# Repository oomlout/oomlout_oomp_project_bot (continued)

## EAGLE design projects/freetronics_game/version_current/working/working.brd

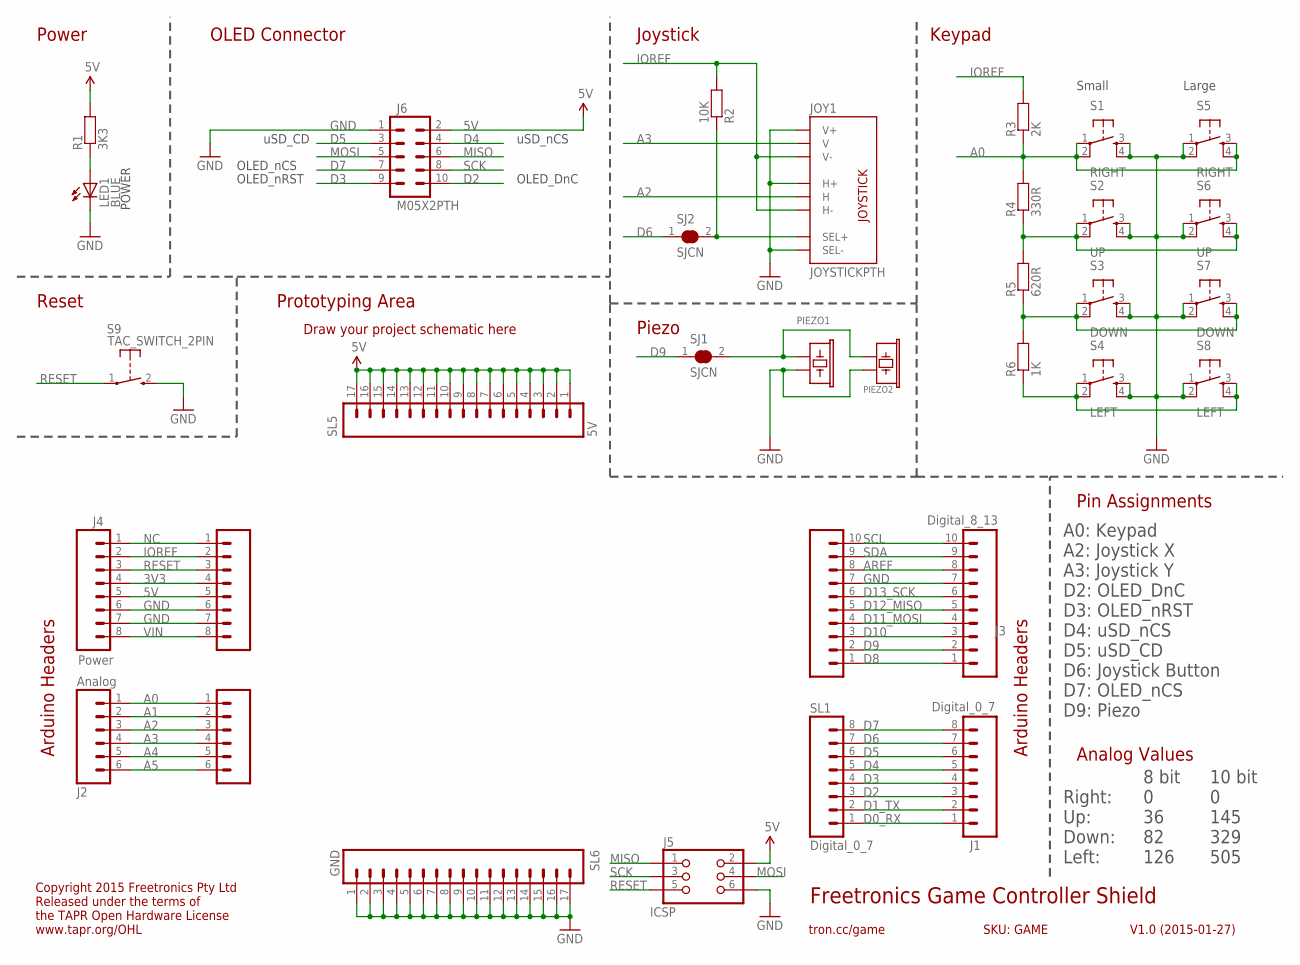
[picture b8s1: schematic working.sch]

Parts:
J1: Digital_0_7; 1X08
J2: Analog; 1X06
J3: Digital_8_13; 1X10
J4: Power; 1X08
J5: ICSP; 2X03PTH
J6: M05X2PTH; AVR_ICSP
JOY1: JOYSTICKPTH; JOYSTICK
LED1: BLUE; LED-0603
PIEZO1: BUZZERSMD12X12; BUZZER-12X12-SMT
PIEZO2: PIEZO12MM
R1: 3K3; 0603
R2: 10K; 0603
R3: 2K; 0603
R4: 330R; 0603
R5: 620R; 0603
R6: 1K; 0603
S1: RIGHT; TACTILE-PTH
S2: UP; TACTILE-PTH
S3: DOWN; TACTILE-PTH
S4: LEFT; TACTILE-PTH
S5: RIGHT; TACTILE-PTH-12MM
S6: UP; TACTILE-PTH-12MM
S7: DOWN; TACTILE-PTH-12MM
S8: LEFT; TACTILE-PTH-12MM
S9: TAC_SWITCH_2PIN; TACTILE_SWITCH_SMD_2PIN_TINY
SJ1, SJ2: SJCN; SJC
SL1: Digital_0_7; 1X08
SL2: Analog; 1X06
SL3: Digital_8_13; 1X10
SL4: Power; 1X08
SL5: 5V; 1X17
SL6: GND; 1X17

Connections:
3V3: J4.4, SL4.4
5V: J4.5, J5.2, J6.2, R1.2, SL4.5, SL5.1, SL5.2, SL5.3, SL5.4, SL5.5, SL5.6, SL5.7, SL5.8, SL5.9, SL5.10, SL5.11, SL5.12, SL5.13, SL5.14, SL5.15, SL5.16, SL5.17
A0: J2.1, R3.1, R4.2, S1.1, S1.2, S5.3, S5.4, SL2.1
A1: J2.2, SL2.2
A2: J2.3, JOY1.H2 (H), SL2.3
A3: J2.4, JOY1.V2 (V), SL2.4
A4: J2.5, SL2.5
A5: J2.6, SL2.6
AREF: J3.8, SL3.8
D0_RX: J1.1, SL1.1
D1_TX: J1.2, SL1.2
D2: J1.3, J6.10, SL1.3
D3: J1.4, J6.9, SL1.4
D4: J1.5, J6.4, SL1.5
D5: J1.6, J6.3, SL1.6
D6: J1.7, SJ2.1, SL1.7
D7: J1.8, J6.7, SL1.8
D8: J3.1, SL3.1
D9: J3.2, SJ1.1, SL3.2
D10: J3.3, SL3.3
D11_MOSI: J3.4, SL3.4
D12_MISO: J3.5, SL3.5
D13_SCK: J3.6, SL3.6
GND: J3.7, J4.6, J4.7, J5.6, J6.1, JOY1.B2A (SEL-), JOY1.H1 (H+), JOY1.V1 (V+), LED1.C, PIEZO1.1, PIEZO2.2, S1.3, S1.4, S2.3, S2.4, S3.3, S3.4, S4.3, S4.4, S5.1, S5.2, S6.1, S6.2, S7.1, S7.2, S8.1, S8.2, S9.2 (S), SL3.7, SL4.6, SL4.7, SL6.1, SL6.2, SL6.3, SL6.4, SL6.5, SL6.6, SL6.7, SL6.8, SL6.9, SL6.10, SL6.11, SL6.12, SL6.13, SL6.14, SL6.15, SL6.16, SL6.17
IOREF: J4.2, JOY1.H3 (H-), JOY1.V3 (V-), R2.2, R3.2, SL4.2
MISO: J5.1, J6.6
MOSI: J5.4, J6.5
unnamed: LED1.A, R1.1
unnamed: PIEZO1.2, PIEZO2.1, SJ1.2
unnamed: JOY1.B1A (SEL+), R2.1, SJ2.2
unnamed: R6.1, S4.1, S4.2, S8.3, S8.4
unnamed: R5.1, R6.2, S3.1, S3.2, S7.3, S7.4
unnamed: R4.1, R5.2, S2.1, S2.2, S6.3, S6.4
NC: J4.1, SL4.1
RESET: J4.3, J5.5, S9.1, SL4.3
SCK: J5.3, J6.8
SCL: J3.10, SL3.10
SDA: J3.9, SL3.9
VIN: J4.8, SL4.8

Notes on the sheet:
Freetronics Game Controller Shield
V1.0 (2015-01-27)
tron.cc/game
SKU: GAME
Arduino Headers
Draw your project schematic here
Copyright 2015 Freetronics Pty Ltd Released under the terms of the TAPR Open Hardware License www.tapr.org/OHL
POWER
OLED_DnC
uSD_CD
OLED_nCS
OLED_nRST
uSD_nCS
Keypad
Joystick
OLED Connector
A0: Keypad A2: Joystick X A3: Joystick Y D2: OLED_DnC D3: OLED_nRST D4: uSD_nCS D5: uSD_CD D6: Joystick Button D7: OLED_nCS D9: Piezo
Power
Reset
Piezo
Prototyping Area
Pin Assignments
10 bit 0 145 329 505
8 bit 0 36 82 126
Right: Up: Down: Left:
Analog Values
Small
Large

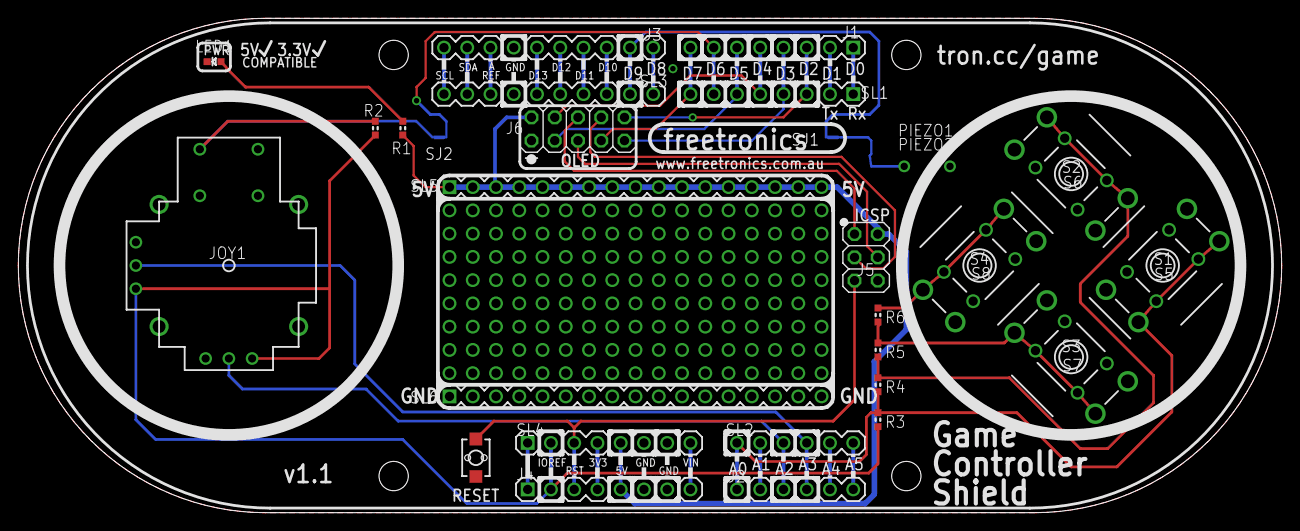
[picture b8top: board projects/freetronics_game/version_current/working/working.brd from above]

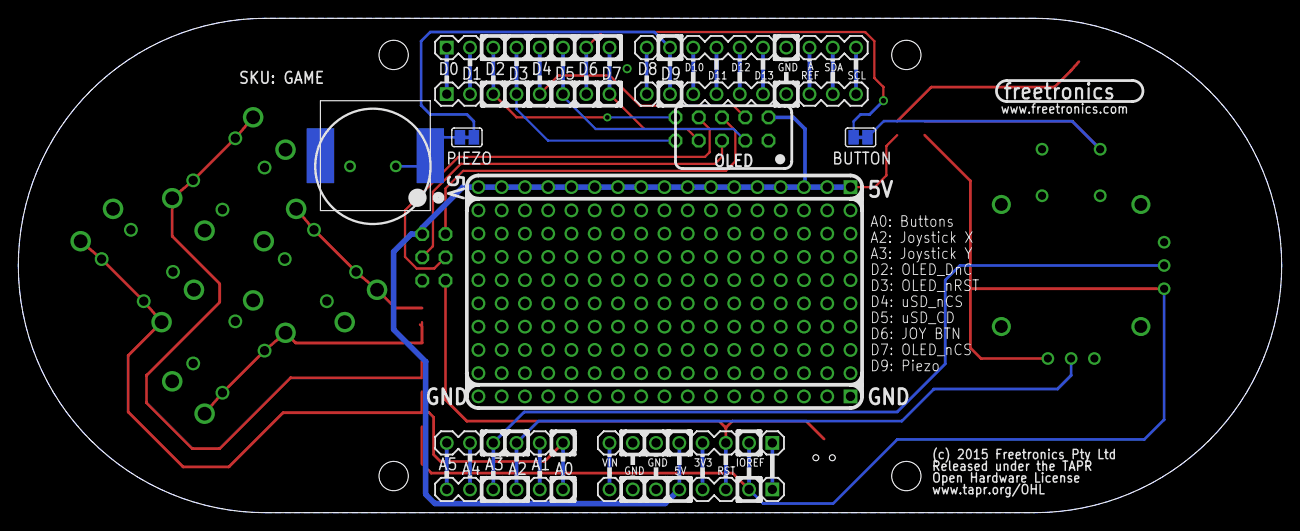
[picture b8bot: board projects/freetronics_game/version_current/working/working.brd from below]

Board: 2 copper layers, 138.0 x 54.0 mm, 33 parts (4 on the bottom side), 39 nets.

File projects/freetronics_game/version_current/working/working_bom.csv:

"Id";"Designator";"Footprint";"Quantity";"Designation";"Supplier and ref";
1;"S7";"TACTILE-PTH-12MM";1;"DOWN";;;
2;"S2";"TACTILE-PTH";1;"UP";;;
3;"SL4,J4";"1X08";2;"Power";;;
4;"S8";"TACTILE-PTH-12MM";1;"LEFT";;;
5;"S9";"TACTILE_SWITCH_SMD_2PIN_TINY";1;"TAC_SWITCH_2PIN";;;
6;"SL2,J2";"1X06";2;"Analog";;;
7;"S4";"TACTILE-PTH";1;"LEFT";;;
8;"R2";"0603";1;"10K";;;
9;"R6";"0603";1;"1K";;;
10;"R3";"0603";1;"2K";;;
11;"LED1";"LED-0603";1;"BLUE";;;
12;"J1,SL1";"1X08";2;"Digital_0_7";;;
13;"SL5";"1X17";1;"5V";;;
14;"SL6";"1X17";1;"GND";;;
15;"JOY1";"JOYSTICK";1;"JOYSTICKPTH";;;
16;"SL3,J3";"1X10";2;"Digital_8_13";;;
17;"@HOLE3,@HOLE0,@HOLE2,@HOLE1";"";4;"";;;
18;"J6";"AVR_ICSP";1;"M05X2PTH";;;
19;"J5";"2X03PTH";1;"ICSP";;;
20;"R5";"0603";1;"620R";;;
21;"R4";"0603";1;"330R";;;
22;"S3";"TACTILE-PTH";1;"DOWN";;;
23;"S5";"TACTILE-PTH-12MM";1;"RIGHT";;;
24;"S1";"TACTILE-PTH";1;"RIGHT";;;
25;"R1";"0603";1;"3K3";;;
26;"S6";"TACTILE-PTH-12MM";1;"UP";;;
27;"PIEZO2";"PIEZO12MM";1;"PIEZO12MM";;;
28;"SJ2,SJ1";"SJC";2;"SJCN";;;
29;"PIEZO1";"BUZZER-12X12-SMT";1;"BUZZERSMD12X12";;;
